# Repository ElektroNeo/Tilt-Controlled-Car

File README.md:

# Tilt-Controlled-Car
Tilt controlled car with PIC microcontroller and MPU6050.

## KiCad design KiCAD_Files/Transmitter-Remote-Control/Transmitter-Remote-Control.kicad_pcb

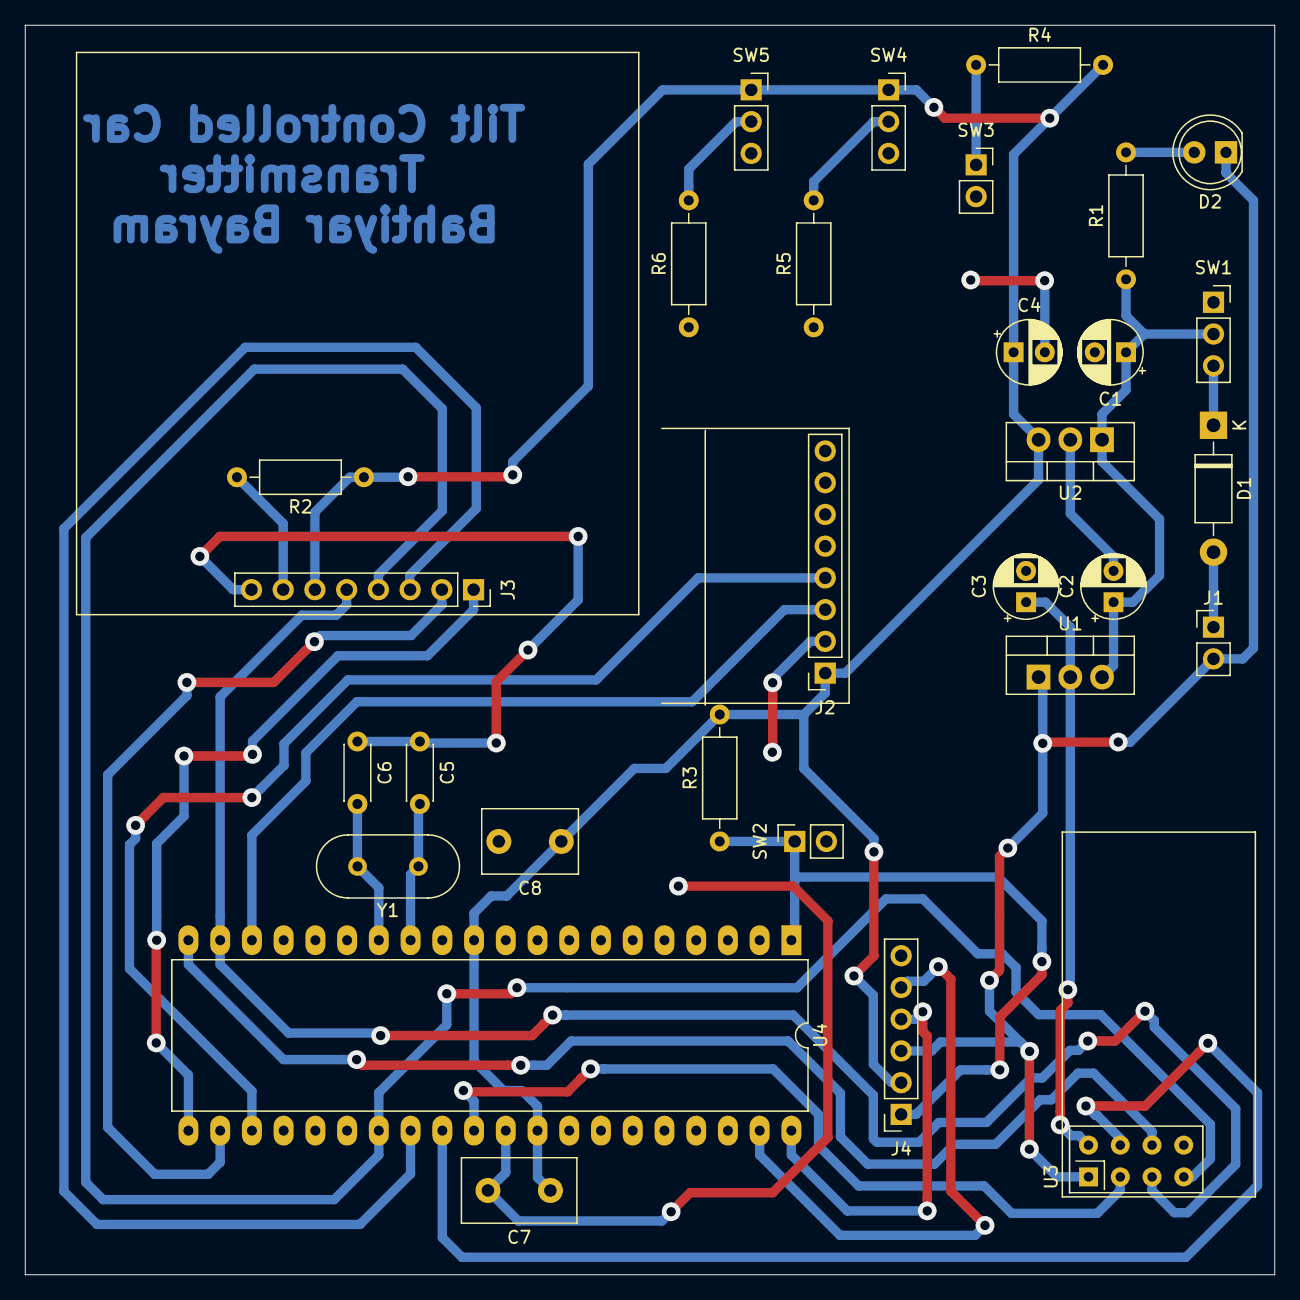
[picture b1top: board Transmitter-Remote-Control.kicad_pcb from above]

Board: 2 copper layers, 100.0 x 100.0 mm, 30 parts (0 on the bottom side), 28 nets.

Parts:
C1, C2, C3, C4: 1uF; CP_Radial_D5.0mm_P2.50mm
C5, C6: 33pF; C_Disc_D4.3mm_W1.9mm_P5.00mm
C7: 100nF; C_Disc_D9.0mm_W5.0mm_P5.00mm
C8: 100nF; C_Disc_D7.5mm_W5.0mm_P5.00mm
D1: 1N4001; D_DO-41_SOD81_P10.16mm_Horizontal
D2: PWR; LED_D5.0mm
J1: PWR_IN; PinHeader_1x02_P2.54mm_Vertical
J2: MPU6050; PinSocket_1x08_P2.54mm_Vertical
J3: NOKIA 5110; PinSocket_1x08_P2.54mm_Vertical
J4: ICSP; PinSocket_1x06_P2.54mm_Vertical
R1: 1k; R_Axial_DIN0207_L6.3mm_D2.5mm_P10.16mm_Horizontal
R2: 330; R_Axial_DIN0207_L6.3mm_D2.5mm_P10.16mm_Horizontal
R3, R4, R5, R6: 10k; R_Axial_DIN0207_L6.3mm_D2.5mm_P10.16mm_Horizontal
SW1: PWR_SW; PinSocket_1x03_P2.54mm_Vertical
SW2: RESET; PinSocket_1x02_P2.54mm_Vertical
SW3: BUTTON; PinSocket_1x02_P2.54mm_Vertical
SW4: SW1; PinSocket_1x03_P2.54mm_Vertical
SW5: SW2; PinSocket_1x03_P2.54mm_Vertical
U1: LM1117-3.3; TO-220-3_Vertical
U2: L7805; TO-220-3_Vertical
U3: NRF24L01_Breakout; nRF24L01_Breakout
U4: PIC18F45K22-IP; DIP-40_W15.24mm_LongPads
Y1: 16MHz; Crystal_HC49-4H_Vertical

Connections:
+3V3: C3.1, U1.2, U3.2
+5V: C4.1, C7.1, C8.1, J2.1, J3.6, J4.2, R2.1, R3.2, R4.2, SW4.1, SW5.1, U2.3, U4.11, U4.32
BTN: R4.1, SW3.1, U4.33
CE: U3.3, U4.30
CE_Nokia: J3.2, U4.22
CLK: J3.5, U3.5, U4.19
DC: J3.3, U4.28
DIN: J3.4, U3.7, U4.27
GND: C1.2, C2.2, C3.2, C4.2, C5.1, C6.1, C7.2, C8.2, D2.1, J1.2, J2.2, J2.7, J3.8, J4.3, SW2.2, SW3.2, SW4.3, SW5.3, U1.1, U2.2, U3.1, U4.12, U4.31
MISO: U3.6, U4.20
unnamed: C5.2, U4.13, Y1.1
unnamed: C6.2, U4.14, Y1.2
unnamed: D1.1, SW1.3
unnamed: D1.2, J1.1
unnamed: D2.2, R1.2
unnamed: J3.7, R2.2
unnamed: R5.2, SW4.2
unnamed: R6.2, SW5.2
PGC: J4.5, U4.39
PGD: J4.4, U4.40
RST: J3.1, U4.21
SCK: J2.3, U4.18
SDA: J2.4, U4.23
SW1: R5.1, U4.34
SW2: R6.1, U4.35
VCC: C1.1, C2.1, R1.1, SW1.2, U1.3, U2.1
~CSN: U3.4, U4.29
~MCLR: J4.1, R3.1, SW2.1, U4.1

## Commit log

2019-04-12 Initialize files
2019-04-14 Add schematics.
2019-04-14 Add Receiver-Car Schematic.
2019-04-14 Added ICSP and optional buttons on transmitter.
2019-04-14 Some files fixed.
2019-05-03 Update schematic.
    - Added switch, buttons and leds.
2019-05-05 Update PCB.
2019-06-03 Update hardware.

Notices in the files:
KiCAD_Files/Transmitter-Remote-Control/Transmitter-Remote-Control.kicad_pcb:
Released under the Creative Commons
